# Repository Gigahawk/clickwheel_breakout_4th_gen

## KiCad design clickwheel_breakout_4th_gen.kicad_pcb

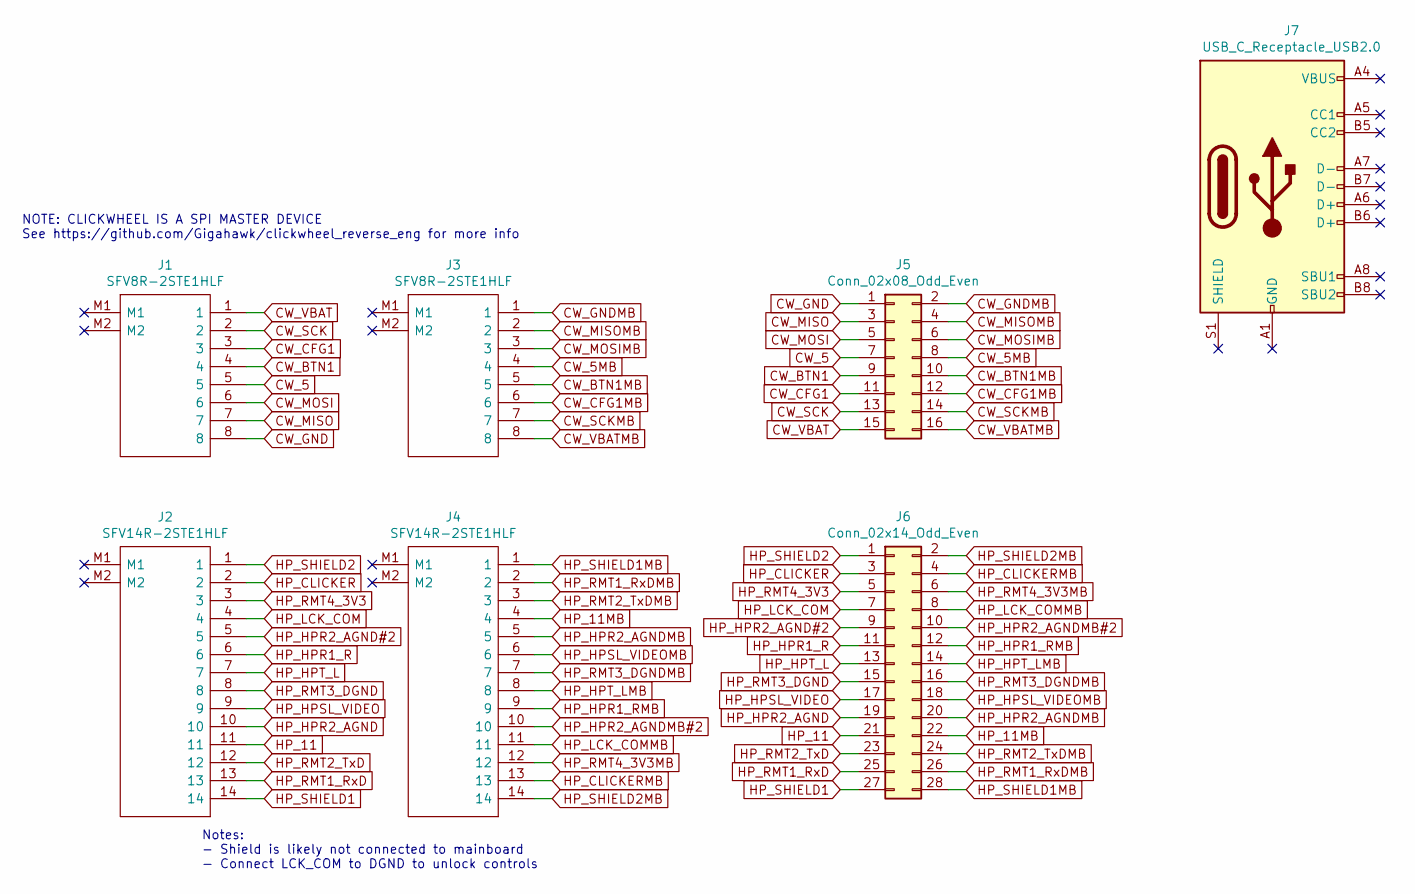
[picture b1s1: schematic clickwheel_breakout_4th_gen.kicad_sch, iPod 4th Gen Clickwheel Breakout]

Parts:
J1, J3: SFV8R-2STE1HLF; SFV8R2STE1HLF; Mouser Part Number 649-SFV8R-2STE1HLF
J2, J4: SFV14R-2STE1HLF; SFV14R2STE1HLF; Manufacturer_Part_Number SFV14R-2STE1HLF
J5: Conn_02x08_Odd_Even; PinHeader_2x08_P2.54mm_Vertical
J6: Conn_02x14_Odd_Even; PinHeader_2x14_P2.54mm_Vertical
J7: USB_C_Receptacle_USB2.0; USB_C_Receptacle_GCT_USB4085

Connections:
CW_5: J1.5, J5.7
CW_5MB: J3.4, J5.8
CW_BTN1: J1.4, J5.9
CW_BTN1MB: J3.5, J5.10
CW_CFG1: J1.3, J5.11
CW_CFG1MB: J3.6, J5.12
CW_GND: J1.8, J5.1
CW_GNDMB: J3.1, J5.2
CW_MISO: J1.7, J5.3
CW_MISOMB: J3.2, J5.4
CW_MOSI: J1.6, J5.5
CW_MOSIMB: J3.3, J5.6
CW_SCK: J1.2, J5.13
CW_SCKMB: J3.7, J5.14
CW_VBAT: J1.1, J5.15
CW_VBATMB: J3.8, J5.16
HP_11: J2.11, J6.21
HP_11MB: J4.4, J6.22
HP_CLICKER: J2.2, J6.3
HP_CLICKERMB: J4.13, J6.4
HP_HPR1_R: J2.6, J6.11
HP_HPR1_RMB: J4.9, J6.12
HP_HPR2_AGND: J2.10, J6.19
HP_HPR2_AGND#2: J2.5, J6.9
HP_HPR2_AGNDMB: J4.5, J6.20
HP_HPR2_AGNDMB#2: J4.10, J6.10
HP_HPSL_VIDEO: J2.9, J6.17
HP_HPSL_VIDEOMB: J4.6, J6.18
HP_HPT_L: J2.7, J6.13
HP_HPT_LMB: J4.8, J6.14
HP_LCK_COM: J2.4, J6.7
HP_LCK_COMMB: J4.11, J6.8
HP_RMT1_RxD: J2.13, J6.25
HP_RMT1_RxDMB: J4.2, J6.26
HP_RMT2_TxD: J2.12, J6.23
HP_RMT2_TxDMB: J4.3, J6.24
HP_RMT3_DGND: J2.8, J6.15
HP_RMT3_DGNDMB: J4.7, J6.16
HP_RMT4_3V3: J2.3, J6.5
HP_RMT4_3V3MB: J4.12, J6.6
HP_SHIELD1: J2.14, J6.27
HP_SHIELD1MB: J4.1, J6.28
HP_SHIELD2: J2.1, J6.1
HP_SHIELD2MB: J4.14, J6.2

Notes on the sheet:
NOTE: CLICKWHEEL IS A SPI MASTER DEVICE See https://github.com/Gigahawk/clickwheel_reverse_eng for more info
Notes: - Shield is likely not connected to mainboard - Connect LCK_COM to DGND to unlock controls

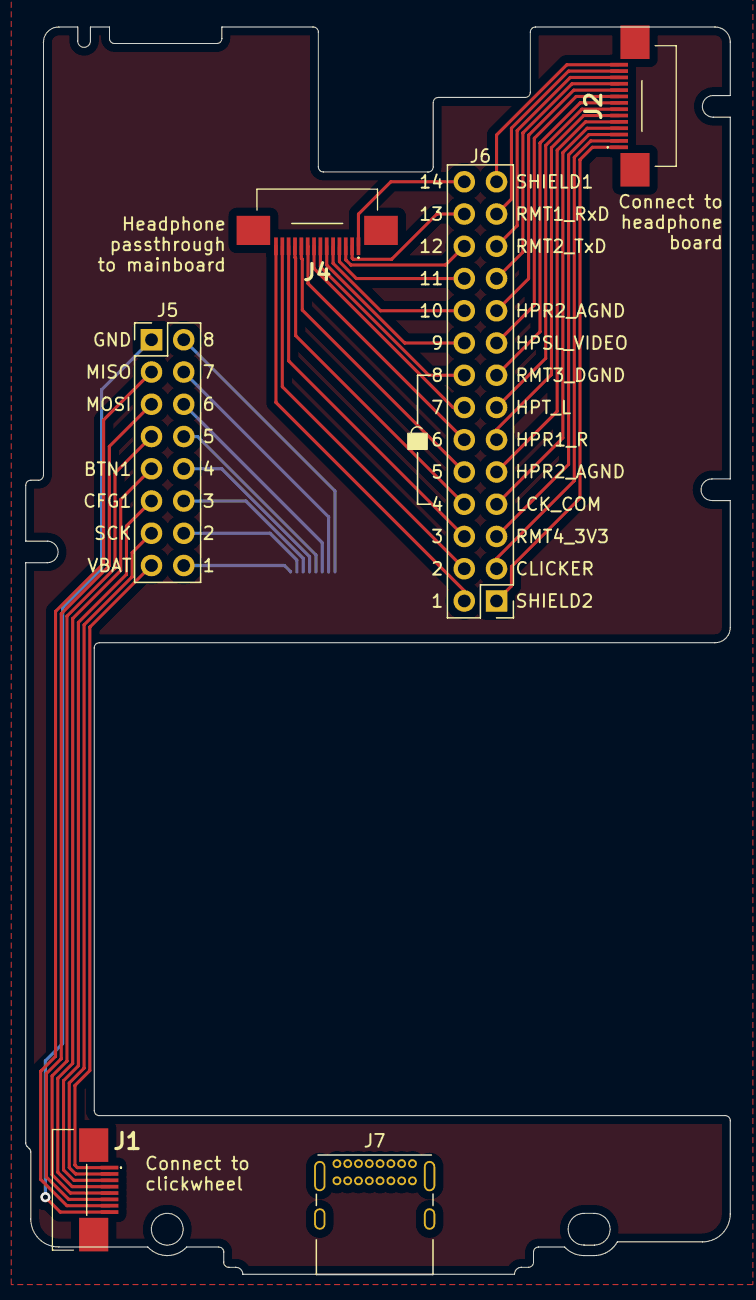
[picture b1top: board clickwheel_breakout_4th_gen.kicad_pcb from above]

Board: 2 copper layers, 55.5 x 98.2 mm, 7 parts (1 on the bottom side), 44 nets.

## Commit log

2020-09-18 Replicate board outline from iPod
2020-09-19 Add Gigahawk.pretty
2020-09-19 Finish layout of connectors
2020-09-19 Add position of clickwheel cable
2020-09-20 Add silkscreens
2020-10-24 Add known clickwheel signal names
2021-11-22 Add known headphone signal names with silkscreen
2022-09-01 kicad: update to kicad 6
2022-09-01 kibot: add initial generated QR code
2022-09-01 [WIP] ci: add CI
2022-09-01 ci: generate qr code text
2022-09-01 ci: generate kibot config to generate qr code
2022-09-01 ci: generate qr symbol/footprint
2022-09-01 ci: generate manufacturing files
2022-09-01 ci: upload outputs
2022-09-01 check diff
2022-09-01 ci: update_qr when generating?
2022-09-01 check fake preflight option
2022-09-01 try verbose output
2022-09-01 fix QR lib name
2022-09-01 fix qr code name
2022-09-01 ci: move qr code to front for now (INTI-CMNB/KiBot#271)
2022-09-01 ci: export schematics
2022-09-01 ci: disable kibot verbose
2022-09-01 ci: cache date so qr code and text match
2022-09-01 ci: generate unique output filenames
2022-09-10 ci: use freecad-export-action to build 3d models
2022-09-10 ci: update checkout to v3, enable submodule checkout for 3d models
2022-09-13 ci: fix 3d model export
2022-09-24 ci: add CI (#1)
2022-09-24 silkscreen: add label for missing headphone AGND
    - silkscreen: add connection instructions
2023-10-04 ci: update to kicad 7
2023-10-04 project: update to kicad 7, remove qr code
2023-10-04 feature: update revision info
2023-10-04 layout: update board thickness
2023-10-04 info: update link to reverse engineering efforts
2023-10-04 schem: update pin names
